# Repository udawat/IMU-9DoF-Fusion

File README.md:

IMU-9DoF-Fusion
===============

Explore Labs' 9 Degrees of Freedom Inertial Measurement Unit with MPU-6150 and HMC5883L and Auto Voltage Level Shifting

To work with the Code, you need the libraries installed at the right place.
Following libraries are required to be copied inside the libraries folder:

I2Cdev - by Jeff Rowberg

MPU6050 - The library for MPU-6050 and MPU-6150 are Code Compatible - by Jeff Rowberg

HMC5883L - by Jeff Rowberg

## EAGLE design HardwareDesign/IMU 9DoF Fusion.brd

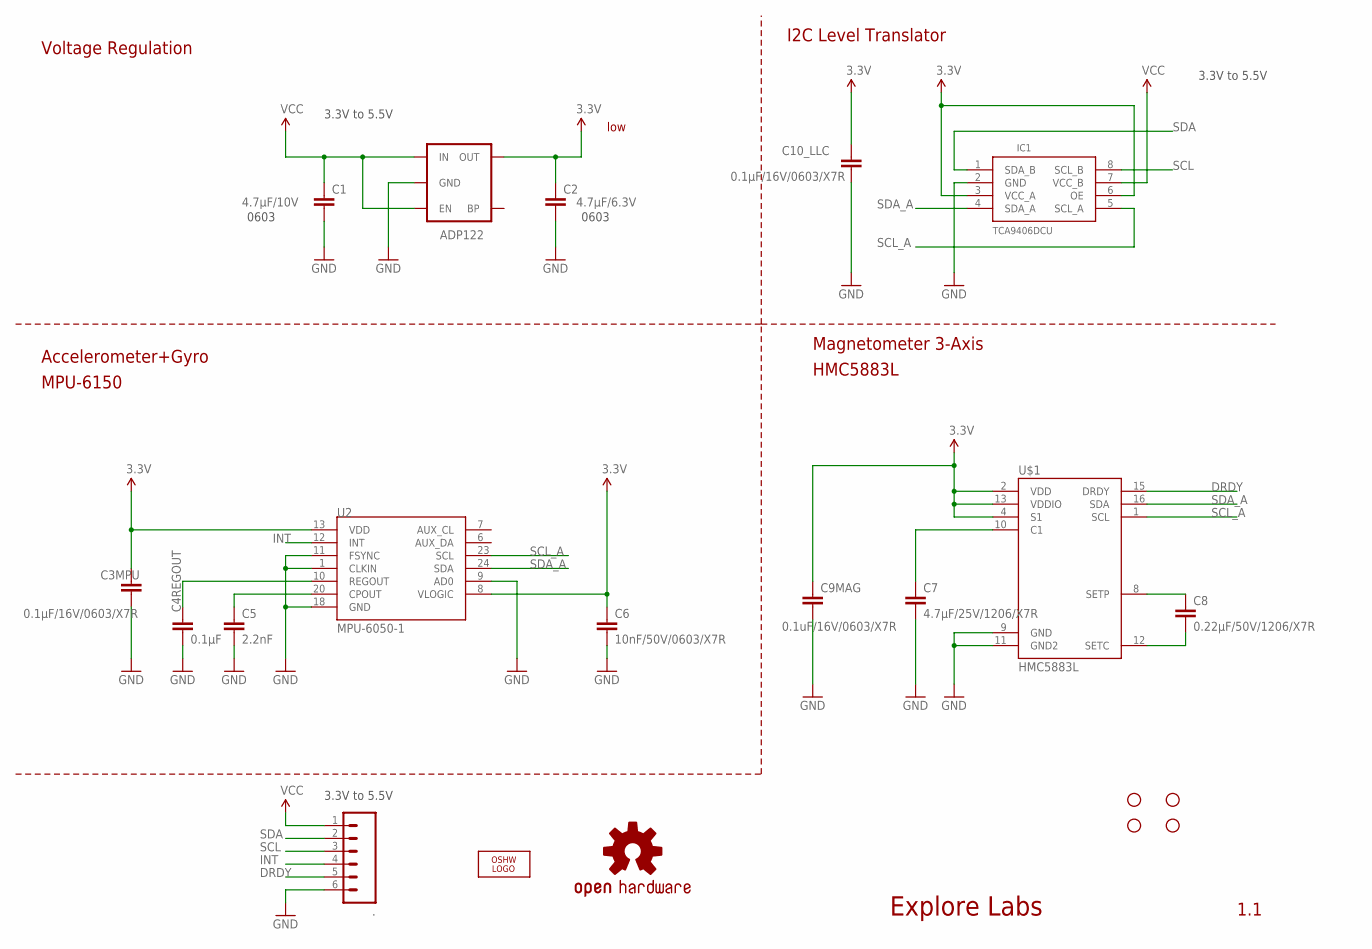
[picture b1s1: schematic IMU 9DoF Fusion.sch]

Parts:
.: M06SIP; 1X06
ADP122: V_REG_LDOSMD; SOT23-5
C1: 4.7µF/10V; 0603-CAP
C2: 4.7µF/6.3V; 0603-CAP
C3MPU, C10_LLC: 0.1µF/16V/0603/X7R; 0603-CAP
C4REGOUT: 0.1µF; 0603-CAP
C5: 2.2nF; 0603-CAP
C6: 10nF/50V/0603/X7R; 0603-CAP
C7: 4.7µF/25V/1206/X7R; 1206
C8: 0.22µF/50V/1206/X7R; 1206
C9MAG: 0.1uF/16V/0603/X7R; 0603-CAP
IC1: TCA9406DCU; VSSOP8
JP1, JP3, JP4, JP5: STAND-OFFTIGHT; STAND-OFF-TIGHT
LOGO1: OSHW_LOGO_FILLX0150-NT; OSHW_FILLX150_NOTEXT
U2: MPU-6050-1; QFN-24-4MM2
U$1: HMC5883L; LPCC16
U$2: OSHW-LOGOS; OSHW-LOGO-S

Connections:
3.3V: ADP122.5 (OUT), C2.1, C3MPU.1, C6.1, C9MAG.1, C10_LLC.1, IC1.3 (VCC_A), IC1.6 (OE), U2.8 (VLOGIC), U2.13 (VDD), U$1.2 (VDD), U$1.4 (S1), U$1.13 (VDDIO)
CPOUT: C5.1, U2.20 (CPOUT)
DRDY: ..5, U$1.15 (DRDY)
GND: ..6, ADP122.2 (GND), C1.2, C2.2, C3MPU.2, C4REGOUT.2, C5.2, C6.2, C7.2, C9MAG.2, C10_LLC.2, IC1.2 (GND), U2.1 (CLKIN), U2.9 (AD0), U2.11 (FSYNC), U2.18 (GND), U$1.9 (GND), U$1.11 (GND2)
INT: ..4, U2.12 (INT)
unnamed: C7.1, U$1.10 (C1)
unnamed: C8.1, U$1.8 (SETP)
unnamed: C8.2, U$1.12 (SETC)
REGOUT: C4REGOUT.1, U2.10 (REGOUT)
SCL: ..3, IC1.8 (SCL_B)
SCL_A: IC1.5 (SCL_A), U2.23 (SCL), U$1.1 (SCL)
SDA: ..2, IC1.1 (SDA_B)
SDA_A: IC1.4 (SDA_A), U2.24 (SDA), U$1.16 (SDA)
VCC: ..1, ADP122.1 (IN), ADP122.3 (EN), C1.1, IC1.7 (VCC_B)

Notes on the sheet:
Explore Labs
1.1
3.3V to 5.5V
I2C Level Translator
Voltage Regulation
MPU-6150
HMC5883L
Magnetometer 3-Axis
Accelerometer+Gyro
0603
low

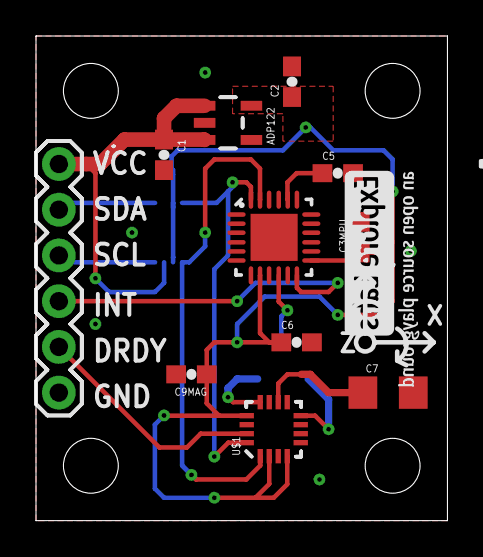
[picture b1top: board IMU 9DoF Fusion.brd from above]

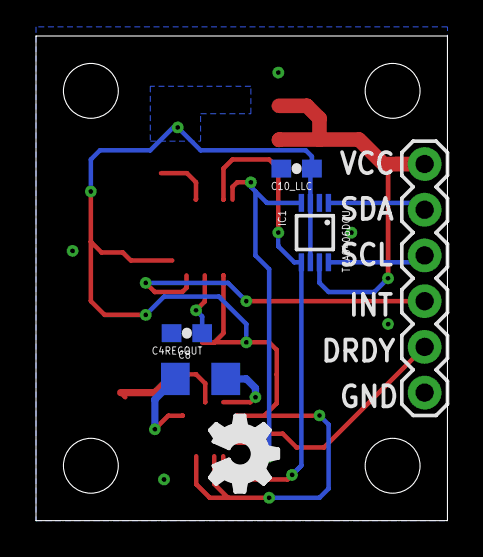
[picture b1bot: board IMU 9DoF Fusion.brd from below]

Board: 2 copper layers, 22.9 x 26.9 mm, 22 parts (6 on the bottom side), 14 nets.

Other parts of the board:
U$3: EXLABS_LOGO_0.25

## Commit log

2013-05-04 initial commit
    added the gerber data with EAGLE files
2013-06-17 moving folders
    changed directory structure
2013-06-17 initial Code example giving raw accel/gyro values with Heading
    compiled from @Jeff Rowberg's I2C Dev Library
2013-06-17 Read it before proceeding
    edited the readme
2013-06-17 ReadMe edits
2013-06-17 Added required arduino libraries
    I2Cdev, MPU6050 and HMC5883L - without these libraries, the code would
    not compile.
2014-01-16 rev 1.1 schematic looks
    EAGLE version updated .epf file.
    Rev 1.1 with minor typo changes.
2014-01-16 schematic in pdf format
    .pdf upload

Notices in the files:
parts and their libraries:
SparkFun-Electromechanical: Licensing: CC v3.0 Share-Alike You are welcome to use this library for commercial purposes.
SparkFun-Aesthetics: Released under the Creative Commons
SparkFun-Aesthetics: http://creativecommons.org/licenses/by-sa/3.0
